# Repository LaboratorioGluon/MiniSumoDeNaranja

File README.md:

# MiniSumoDeNaranja
Minisumo para la competición OSHDEM 2023.

Hecho integramente en los directos de twitch (www.twitch.tv/labgluon)

# Hardware

## Componentes (fuera de la PCB):
- Sensores IR (TCRT5000) https://s.click.aliexpress.com/e/_DeqiwYr
- Sensores ToF (VL53L0X) https://s.click.aliexpress.com/e/_DDpGy5Z
- Motores (N20 200RPM) https://s.click.aliexpress.com/e/_DkiL8JH
- ESP32 (ESP32-WROOM-32D) https://s.click.aliexpress.com/e/_DlMmuSj

## Configuracion pines

| 1 | 2 | 3 | 4 | Modo |
|-|-|-|-|-|
| 0 | 0 | 0 | 0 | FWD  |
| 1 | 0 | 0 | 0 | RIGHT|
| 0 | 1 | 0 | 0 | LEFT |

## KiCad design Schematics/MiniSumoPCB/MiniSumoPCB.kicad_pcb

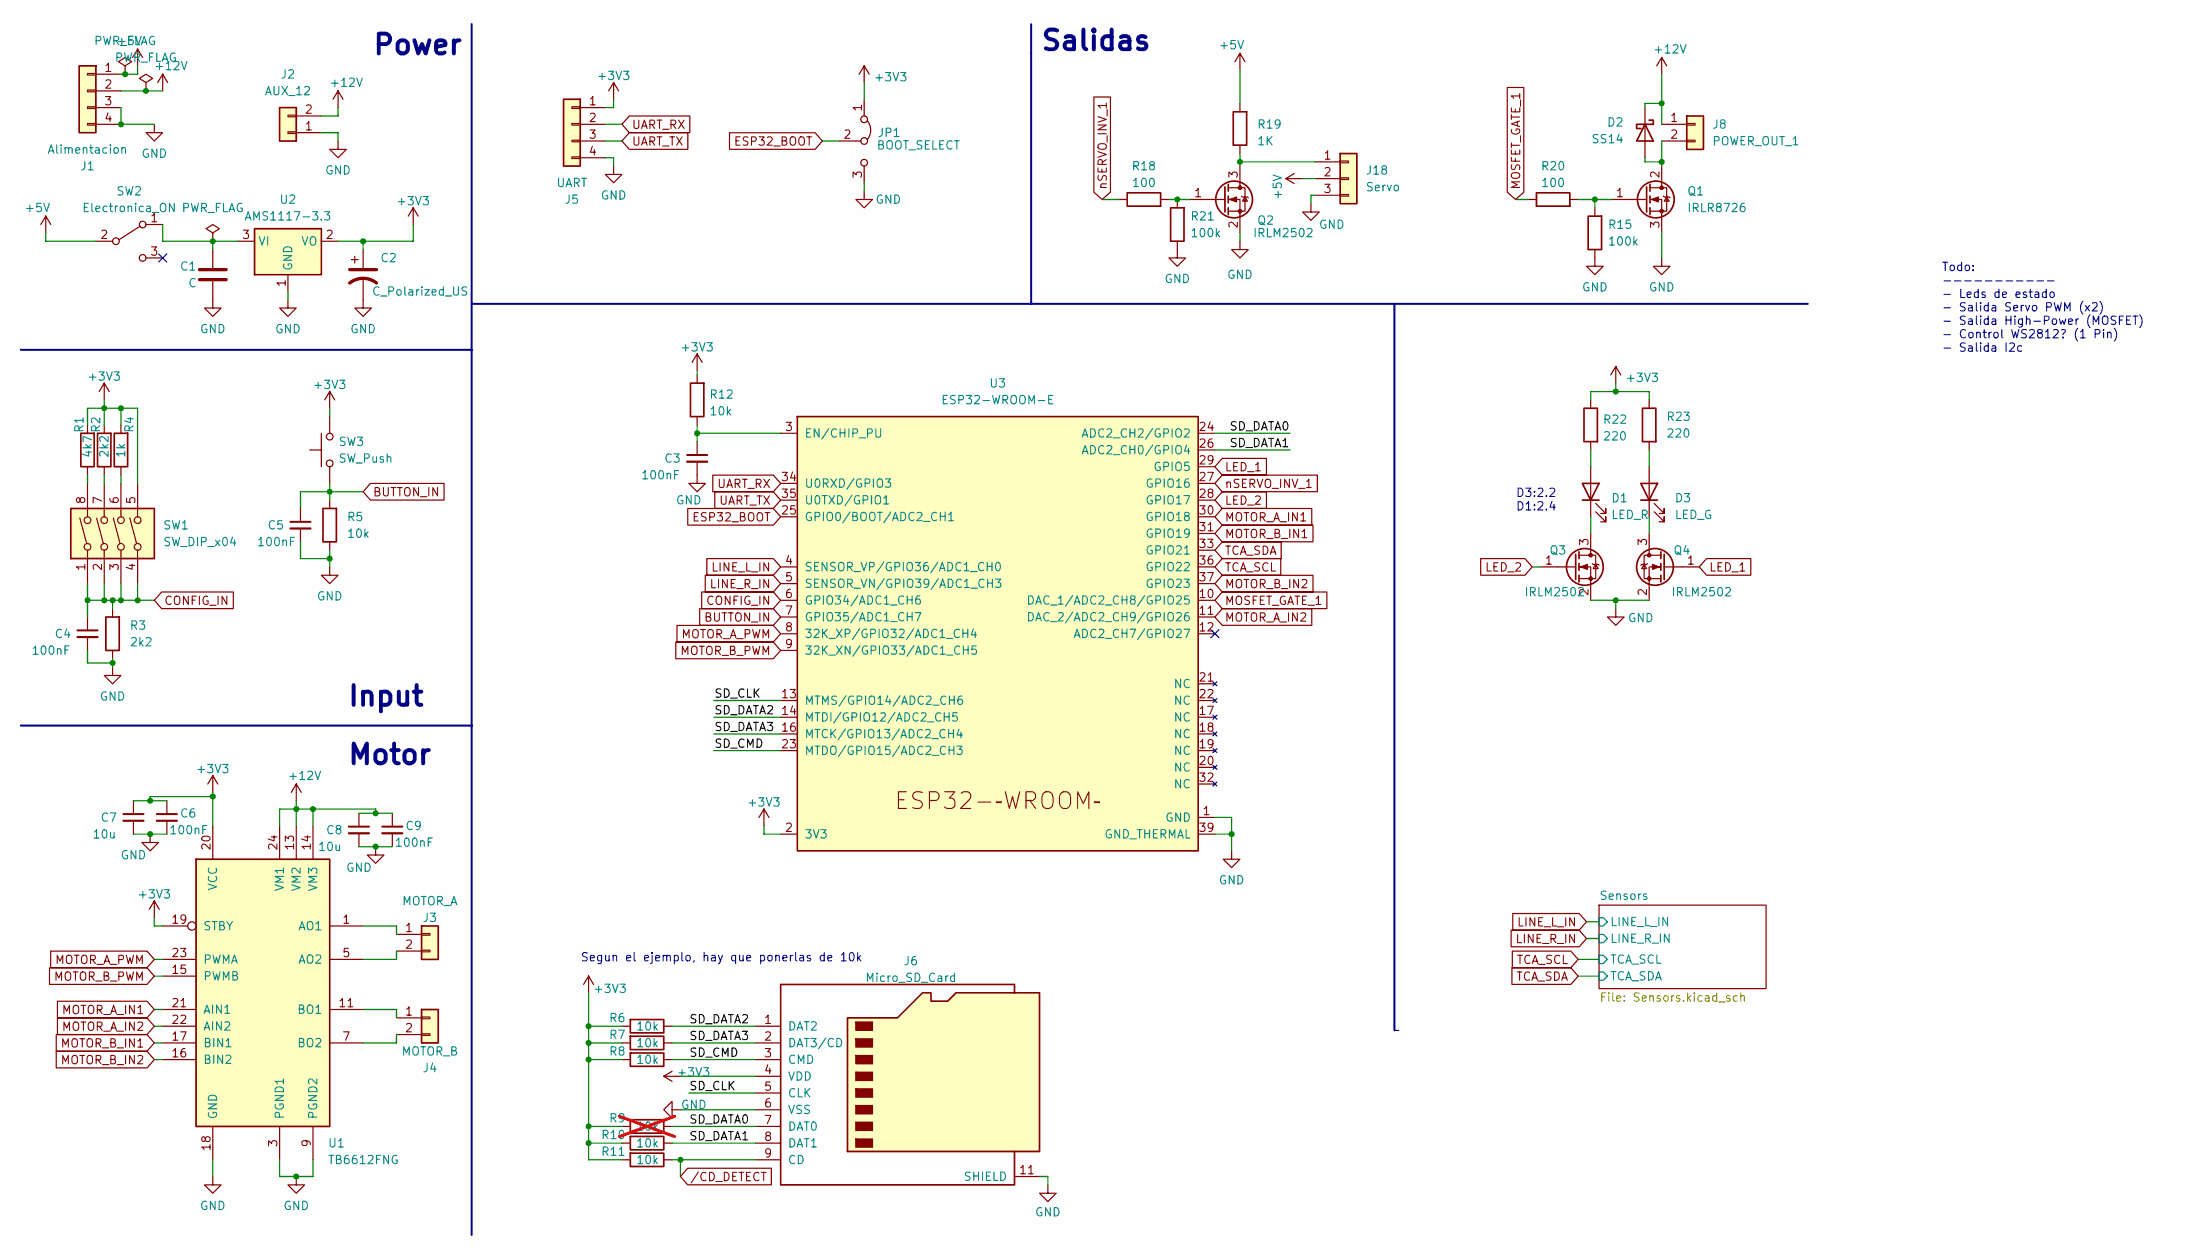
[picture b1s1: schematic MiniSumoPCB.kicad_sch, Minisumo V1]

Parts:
C1: C; C_1206_3216Metric_Pad1.33x1.80mm_HandSolder
C2: C_Polarized_US; CP_Elec_4x5.3
C3, C4, C5, C6, C9: 100nF; C_1206_3216Metric_Pad1.33x1.80mm_HandSolder
C7, C8: 10u; C_1206_3216Metric_Pad1.33x1.80mm_HandSolder
D1: LED_R; LED_1210_3225Metric_Pad1.42x2.65mm_HandSolder
D2: SS14; D_SMA_Handsoldering
D3: LED_G; LED_1210_3225Metric_Pad1.42x2.65mm_HandSolder
J1: Alimentacion; JST_PH_B4B-PH-K_1x04_P2.00mm_Vertical
J2: AUX_12; S2B-XH-SM4-TB
J3: MOTOR_A; S2B-XH-SM4-TB
J4: MOTOR_B; S2B-XH-SM4-TB
J5: UART; PinHeader_1x04_P2.54mm_Vertical
J6: Micro_SD_Card; microSD-Receptacle-SelfEject
J8: POWER_OUT_1; S2B-XH-SM4-TB
J18: Servo; PinHeader_1x03_P2.54mm_Vertical
JP1: BOOT_SELECT; PinHeader_1x03_P2.54mm_Vertical
Q1: IRLR8726; TO-252-2
Q2, Q3, Q4: IRLM2502; SOT-23
R1: 4k7; R_1206_3216Metric_Pad1.30x1.75mm_HandSolder
R2, R3: 2k2; R_1206_3216Metric_Pad1.30x1.75mm_HandSolder
R4: 1k; R_1206_3216Metric_Pad1.30x1.75mm_HandSolder
R5, R6, R7, R8, R10, R11, R12: 10k; R_1206_3216Metric_Pad1.30x1.75mm_HandSolder
R9: 10k; R_1206_3216Metric_Pad1.30x1.75mm_HandSolder; not fitted
R15, R21: 100k; R_1206_3216Metric_Pad1.30x1.75mm_HandSolder
R18, R20: 100; R_1206_3216Metric_Pad1.30x1.75mm_HandSolder
R19: 1K; R_1206_3216Metric_Pad1.30x1.75mm_HandSolder
R22, R23: 220; R_1206_3216Metric_Pad1.30x1.75mm_HandSolder
SW1: SW_DIP_x04; SW_DIP_SPSTx04_Slide_9.78x12.34mm_W7.62mm_P2.54mm
SW2: Electronica_ON; SS12D07VG2
SW3: SW_Push; SKPMANE010 _Silicone_6x6mm
U1: TB6612FNG; SSOP-24_5.3x8.2mm_P0.65mm
U2: AMS1117-3.3; SOT-223-3_TabPin2
U3: ESP32-WROOM-E; ESP32-WROOM-32E

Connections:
+3V3: C2.1, C6.1, C7.1, J5.1, J6.4 (VDD), JP1.1 (A), R1.2, R2.2, R4.2, R6.2, R7.2, R8.2, R9.2, R10.2, R11.2, R12.2, R22.1, R23.1, SW1.5, SW3.2, U1.19 (STBY), U1.20 (VCC), U2.2 (VO), U3.2 (3V3); also elsewhere on the board
+5V: J1.1, J18.2, R19.2, SW2.2 (B)
+12V: C8.1, C9.1, D2.1 (K), J1.2, J2.2, J8.1, U1.13 (VM2), U1.14 (VM3), U1.24 (VM1)
/SD_CLK: J6.5 (CLK), U3.13 (MTMS/GPIO14/ADC2_CH6)
/SD_CMD: J6.3 (CMD), R8.1, U3.23 (MTDO/GPIO15/ADC2_CH3)
/SD_DATA0: J6.7 (DAT0), R9.1, U3.24 (ADC2_CH2/GPIO2)
/SD_DATA1: J6.8 (DAT1), R10.1, U3.26 (ADC2_CH0/GPIO4)
/SD_DATA2: J6.1 (DAT2), R6.1, U3.14 (MTDI/GPIO12/ADC2_CH5)
/SD_DATA3: J6.2 (DAT3/CD), R7.1, U3.16 (MTCK/GPIO13/ADC2_CH4)
BUTTON_IN: C5.1, R5.2, SW3.1, U3.7 (GPIO35/ADC1_CH7)
CONFIG_IN: C4.1, R3.2, SW1.1, SW1.2, SW1.3, SW1.4, U3.6 (GPIO34/ADC1_CH6)
ESP32_BOOT: JP1.2 (C), U3.25 (GPIO0/BOOT/ADC2_CH1)
GND: C1.2, C2.2, C3.2, C4.2, C5.2, C6.2, C7.2, C8.2, C9.2, J1.3, J1.4, J2.1, J5.4, J6.6 (VSS), J6.11 (SHIELD), J18.3, JP1.3 (B), Q1.3 (S), Q2.2 (S), Q3.2 (S), Q4.2 (S), R3.1, R5.1, R15.1, R21.1, U1.3 (PGND1), U1.4 (PGND1), U1.9 (PGND2), U1.10 (PGND2), U1.18 (GND), U2.1 (GND), U3.1 (GND), U3.15 (GND), U3.38 (GND), U3.39 (GND_THERMAL); also elsewhere on the board
LED_1: Q4.1 (G), U3.29 (GPIO5)
LED_2: Q3.1 (G), U3.28 (GPIO17)
LINE_L_IN: U3.4 (SENSOR_VP/GPIO36/ADC1_CH0); also elsewhere on the board
LINE_R_IN: U3.5 (SENSOR_VN/GPIO39/ADC1_CH3); also elsewhere on the board
MOSFET_GATE_1: R20.1, U3.10 (DAC_1/ADC2_CH8/GPIO25)
MOTOR_A_IN1: U1.21 (AIN1), U3.30 (GPIO18)
MOTOR_A_IN2: U1.22 (AIN2), U3.11 (DAC_2/ADC2_CH9/GPIO26)
MOTOR_A_PWM: U1.23 (PWMA), U3.8 (32K_XP/GPIO32/ADC1_CH4)
MOTOR_B_IN1: U1.17 (BIN1), U3.31 (GPIO19)
MOTOR_B_IN2: U1.16 (BIN2), U3.37 (GPIO23)
MOTOR_B_PWM: U1.15 (PWMB), U3.9 (32K_XN/GPIO33/ADC1_CH5)
unnamed: D1.2 (A), R22.2
unnamed: D1.1 (K), Q3.3 (D)
unnamed: D2.2 (A), J8.2, Q1.2 (D)
unnamed: D3.2 (A), R23.2
unnamed: D3.1 (K), Q4.3 (D)
unnamed: J3.1, U1.1 (AO1), U1.2 (AO1)
unnamed: J3.2, U1.5 (AO2), U1.6 (AO2)
unnamed: J4.1, U1.11 (BO1), U1.12 (BO1)
unnamed: J4.2, U1.7 (BO2), U1.8 (BO2)
unnamed: J18.1, Q2.3 (D), R19.1
unnamed: Q1.1 (G), R15.2, R20.2
unnamed: Q2.1 (G), R18.2, R21.2
unnamed: R1.1, SW1.8
unnamed: R2.1, SW1.7
unnamed: R4.1, SW1.6
unnamed: C1.1, SW2.1 (A), U2.3 (VI)
unnamed: C3.1, R12.1, U3.3 (EN/CHIP_PU)
TCA_SCL: U3.36 (GPIO22); also elsewhere on the board
TCA_SDA: U3.33 (GPIO21); also elsewhere on the board
UART_RX: J5.2, U3.34 (U0RXD/GPIO3)
UART_TX: J5.3, U3.35 (U0TXD/GPIO1)
nSERVO_INV_1: R18.1, U3.27 (GPIO16)
/CD_DETECT: J6.9 (CD), R11.1

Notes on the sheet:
Motor
Segun el ejemplo, hay que ponerlas de 10k
Power
Salidas
D3:2.2 D1:2.4
Todo: ----------- - Leds de estado - Salida Servo PWM (x2) - Salida High-Power (MOSFET) - Control WS2812? (1 Pin) - Salida I2c
Input

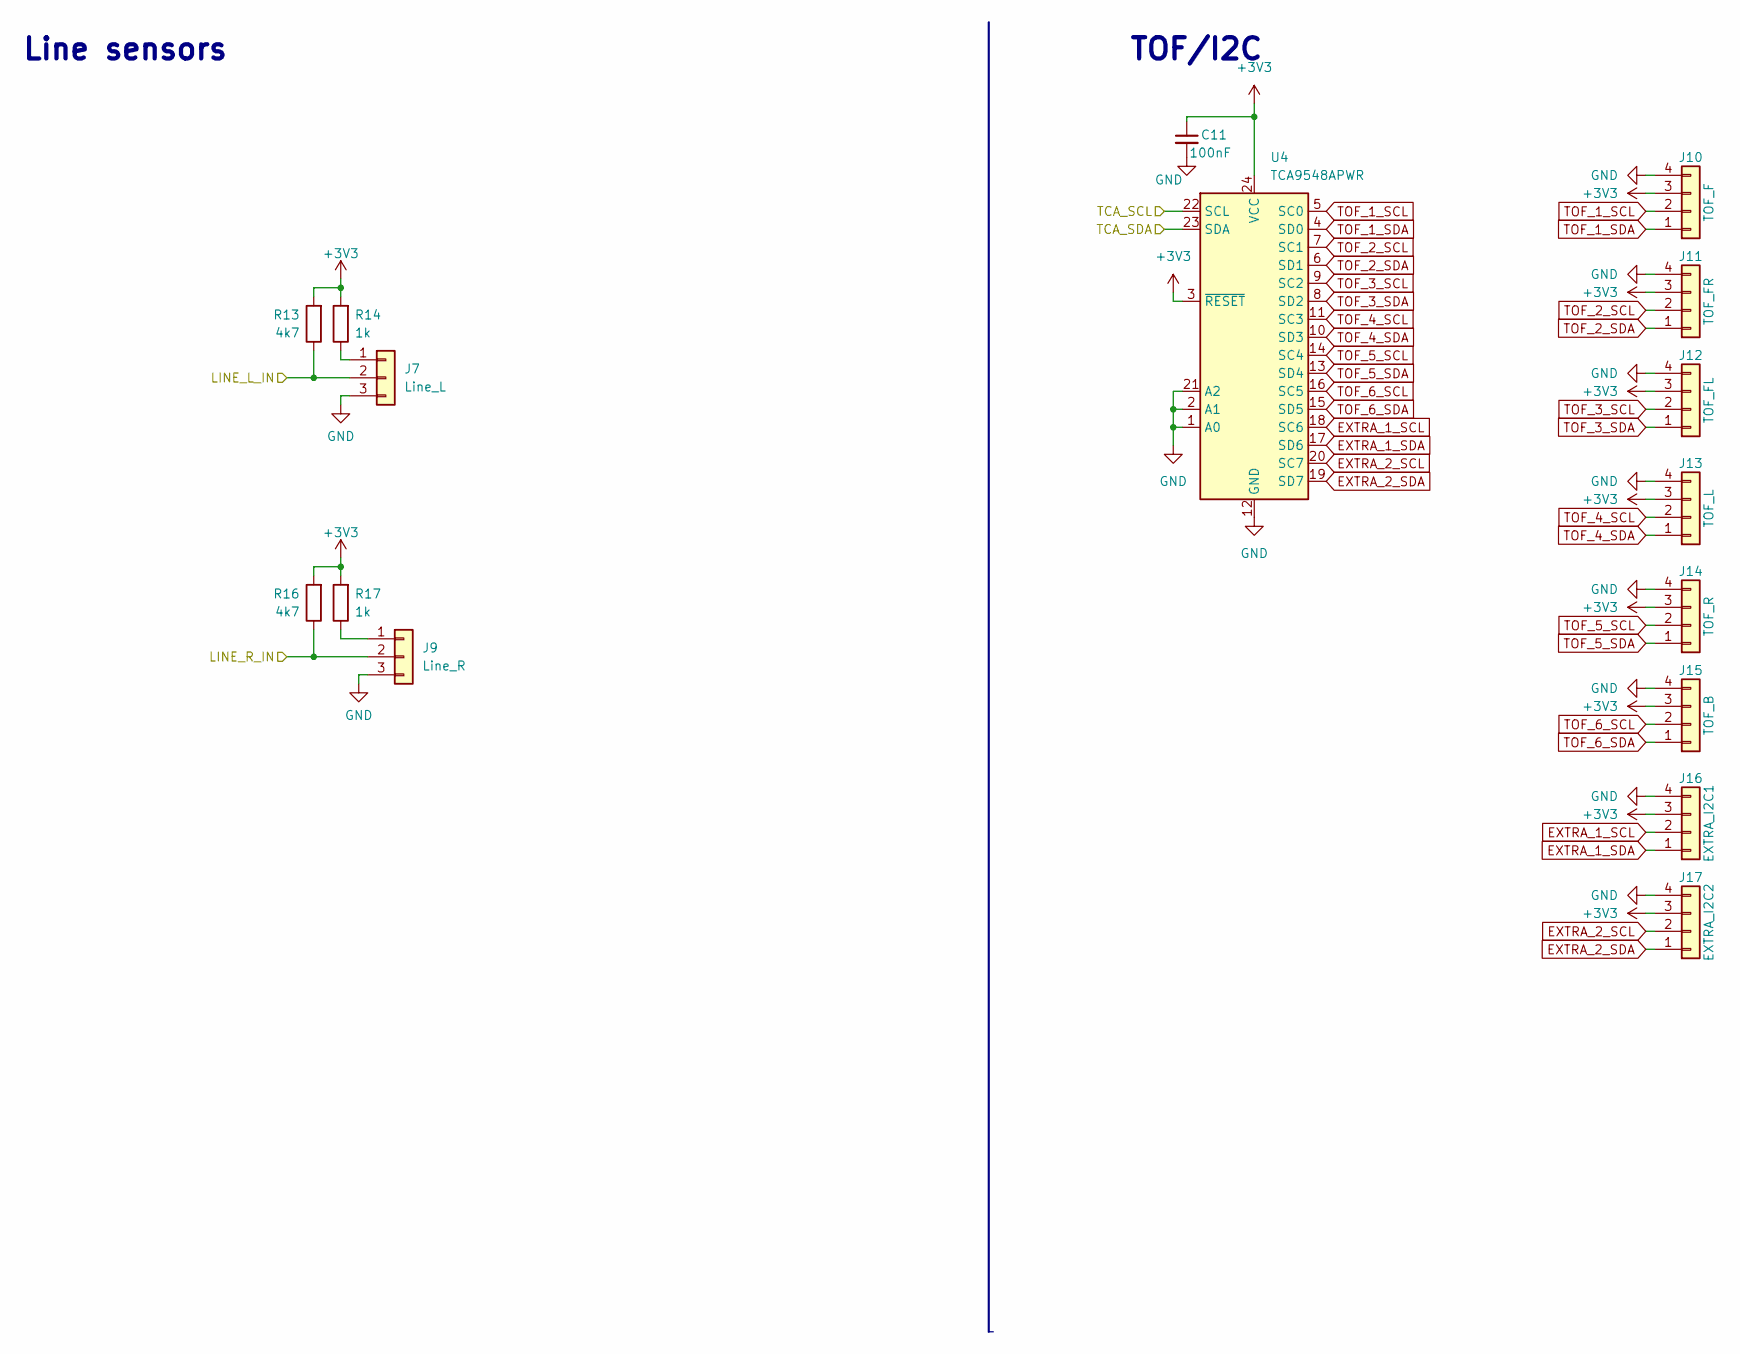
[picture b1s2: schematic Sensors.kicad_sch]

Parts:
C11: 100nF; C_1206_3216Metric_Pad1.33x1.80mm_HandSolder
J7: Line_L; JST_PH_B3B-PH-K_1x03_P2.00mm_Vertical
J9: Line_R; JST_PH_B3B-PH-K_1x03_P2.00mm_Vertical
J10: TOF_F; JST_PH_B4B-PH-K_1x04_P2.00mm_Vertical
J11: TOF_FR; JST_PH_B4B-PH-K_1x04_P2.00mm_Vertical
J12: TOF_FL; JST_PH_B4B-PH-K_1x04_P2.00mm_Vertical
J13: TOF_L; JST_PH_B4B-PH-K_1x04_P2.00mm_Vertical
J14: TOF_R; JST_PH_B4B-PH-K_1x04_P2.00mm_Vertical
J15: TOF_B; JST_PH_B4B-PH-K_1x04_P2.00mm_Vertical
J16: EXTRA_I2C1; JST_PH_B4B-PH-K_1x04_P2.00mm_Vertical
J17: EXTRA_I2C2; JST_PH_B4B-PH-K_1x04_P2.00mm_Vertical
R13, R16: 4k7; R_1206_3216Metric_Pad1.30x1.75mm_HandSolder
R14, R17: 1k; R_1206_3216Metric_Pad1.30x1.75mm_HandSolder
U4: TCA9548APWR; TSSOP-24_4.4x7.8mm_P0.65mm

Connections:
+3V3: C11.1, J10.3, J11.3, J12.3, J13.3, J14.3, J15.3, J16.3, J17.3, R13.2, R14.2, R16.2, R17.2, U4.3 (~RESET), U4.24 (VCC); also elsewhere on the board
EXTRA_1_SCL: J16.2, U4.18 (SC6)
EXTRA_1_SDA: J16.1, U4.17 (SD6)
EXTRA_2_SCL: J17.2, U4.20 (SC7)
EXTRA_2_SDA: J17.1, U4.19 (SD7)
GND: C11.2, J7.3, J9.3, J10.4, J11.4, J12.4, J13.4, J14.4, J15.4, J16.4, J17.4, U4.1 (A0), U4.2 (A1), U4.12 (GND), U4.21 (A2); also elsewhere on the board
LINE_L_IN: J7.2, R13.1; also elsewhere on the board
LINE_R_IN: J9.2, R16.1; also elsewhere on the board
unnamed: J7.1, R14.1
unnamed: J9.1, R17.1
TCA_SCL: U4.22 (SCL); also elsewhere on the board
TCA_SDA: U4.23 (SDA); also elsewhere on the board
TOF_1_SCL: J10.2, U4.5 (SC0)
TOF_1_SDA: J10.1, U4.4 (SD0)
TOF_2_SCL: J11.2, U4.7 (SC1)
TOF_2_SDA: J11.1, U4.6 (SD1)
TOF_3_SCL: J12.2, U4.9 (SC2)
TOF_3_SDA: J12.1, U4.8 (SD2)
TOF_4_SCL: J13.2, U4.11 (SC3)
TOF_4_SDA: J13.1, U4.10 (SD3)
TOF_5_SCL: J14.2, U4.14 (SC4)
TOF_5_SDA: J14.1, U4.13 (SD4)
TOF_6_SCL: J15.2, U4.16 (SC5)
TOF_6_SDA: J15.1, U4.15 (SD5)

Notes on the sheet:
Line sensors
TOF/I2C

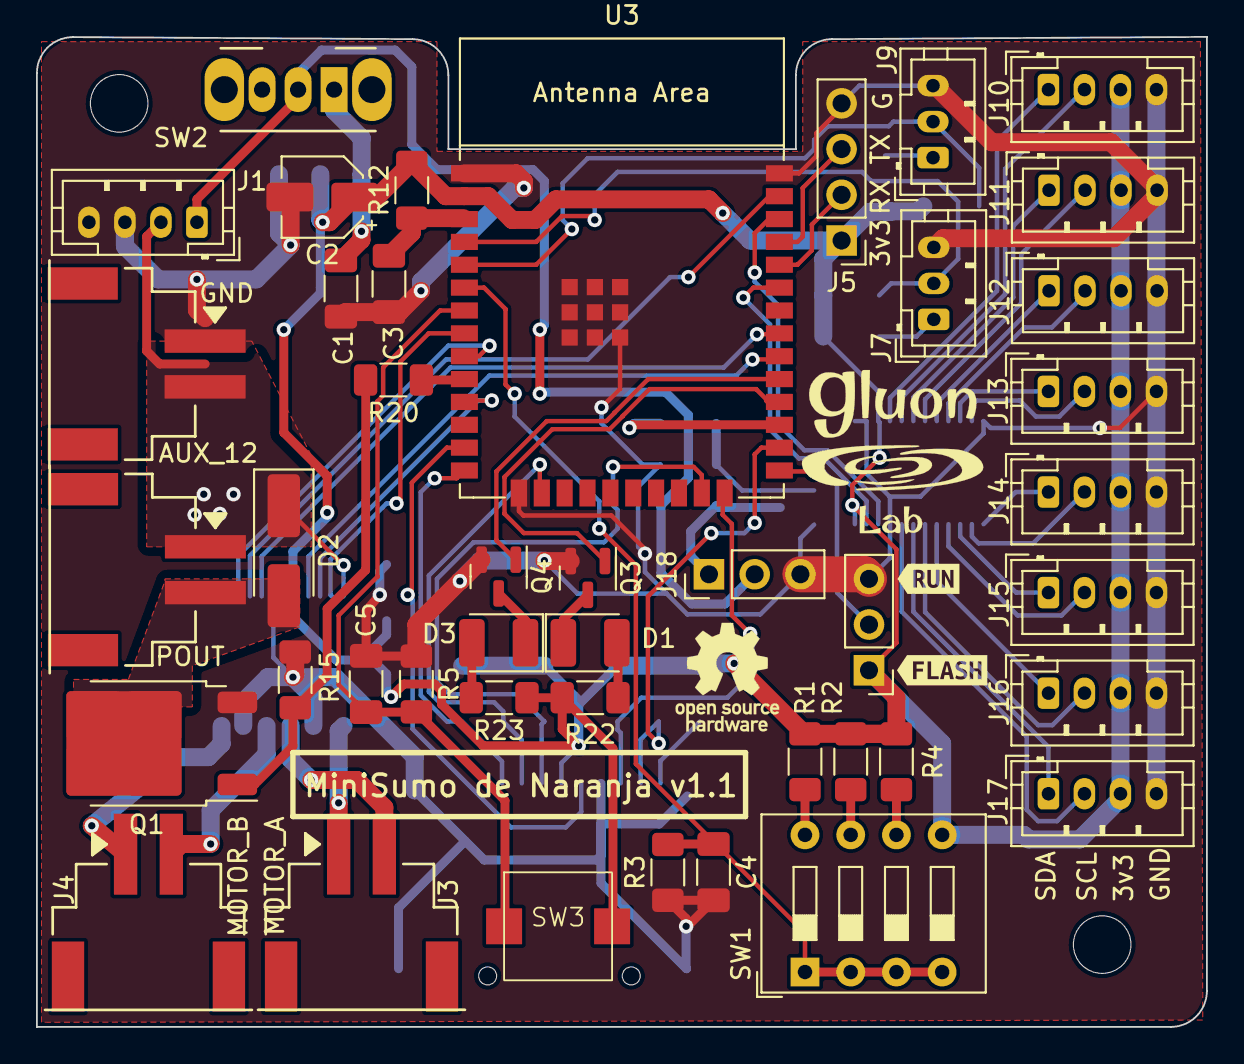
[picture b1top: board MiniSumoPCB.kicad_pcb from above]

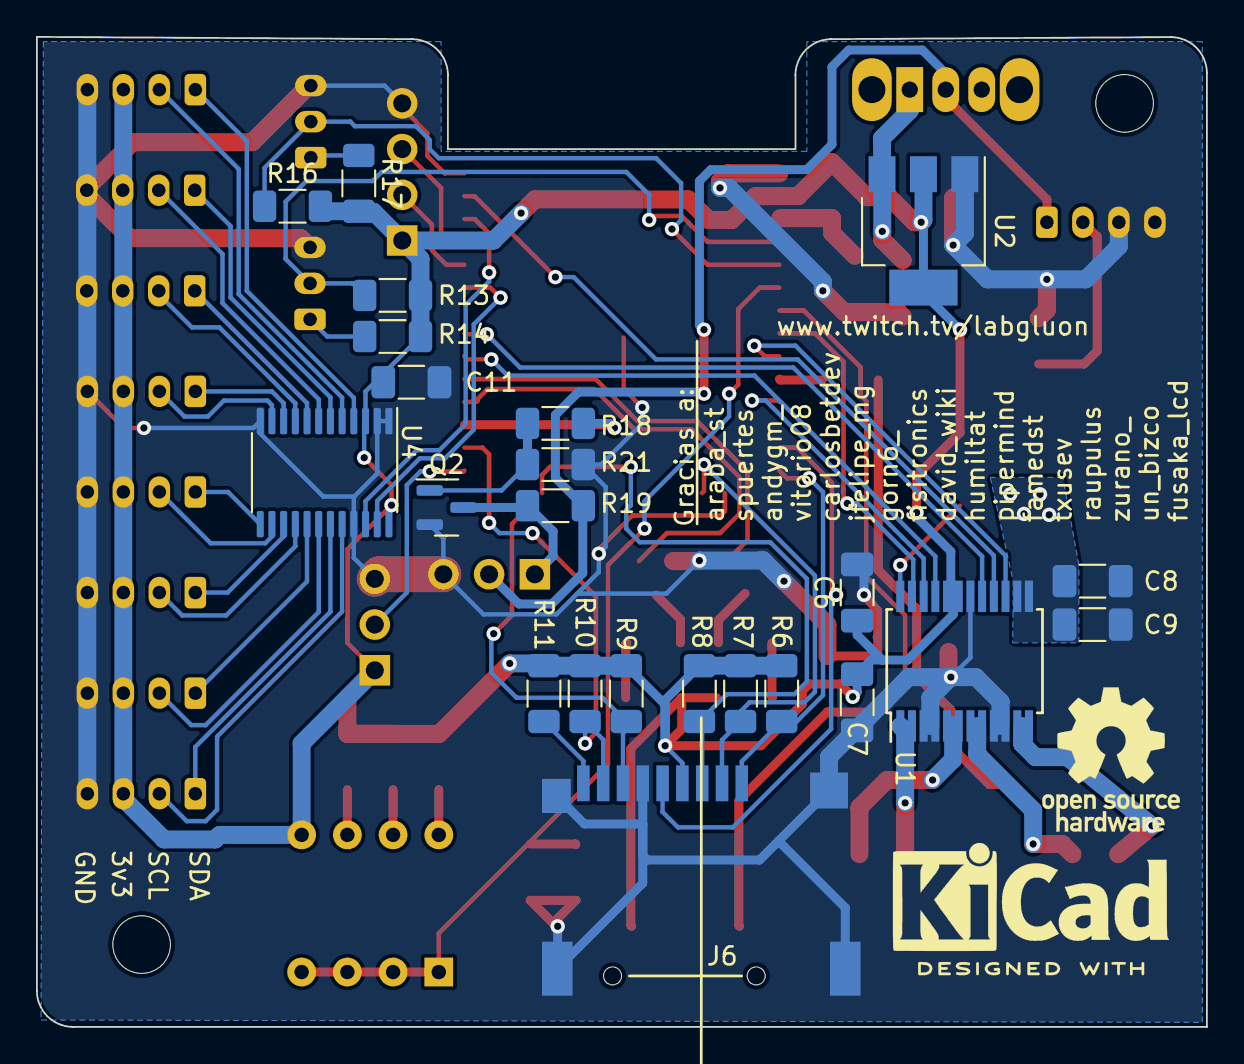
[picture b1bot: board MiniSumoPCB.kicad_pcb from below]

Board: 2 copper layers, 65.0 x 55.0 mm, 68 parts (23 on the bottom side), 65 nets.

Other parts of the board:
kibuzzard-63F11F4E: G***; kibuzzard-63F11F4E
kibuzzard-63F11F5A: G***; kibuzzard-63F11F5A

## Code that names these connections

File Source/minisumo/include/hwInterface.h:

// Pinout for U3 (ESP32-WROOM-E)
// #define PIN_GND 
// #define PIN_P3V3 
#define PIN_NETNU3NENSLASHCHIP_PU 
#define PIN_LINE_L_IN GPIO_NUM_36
#define PIN_LINE_R_IN GPIO_NUM_39
#define PIN_CONFIG_IN GPIO_NUM_34
#define PIN_BUTTON_IN GPIO_NUM_35
#define PIN_MOTOR_A_PWM GPIO_NUM_32
#define PIN_MOTOR_B_PWM GPIO_NUM_33
#define PIN_MOSFET_GATE_1 GPIO_NUM_25
#define PIN_MOTOR_A_IN2 GPIO_NUM_26
// #define PIN_UNCONNECTEDNU3NADC2_CH7SLASHGPIO27NPAD12 GPIO_NUM_27
#define PIN_SD_CLK GPIO_NUM_14
#define PIN_SD_DATA2 GPIO_NUM_12
#define PIN_GND 
#define PIN_SD_DATA3 GPIO_NUM_13
// #define PIN_UNCONNECTEDNU3NNCNPAD17 
// #define PIN_UNCONNECTEDNU3NNCNPAD18 
// #define PIN_UNCONNECTEDNU3NNCNPAD19 
// #define PIN_UNCONNECTEDNU3NNCNPAD20 
// #define PIN_UNCONNECTEDNU3NNCNPAD21 
// #define PIN_UNCONNECTEDNU3NNCNPAD22 
#define PIN_SD_CMD GPIO_NUM_15
#define PIN_SD_DATA0 GPIO_NUM_2
#define PIN_ESP32_BOOT GPIO_NUM_0
#define PIN_SD_DATA1 GPIO_NUM_4
#define PIN_NSERVO_INV_1 GPIO_NUM_16
#define PIN_LED_2 GPIO_NUM_17
#define PIN_LED_1 GPIO_NUM_5
#define PIN_MOTOR_A_IN1 GPIO_NUM_18
#define PIN_MOTOR_B_IN1 GPIO_NUM_19
// #define PIN_UNCONNECTEDNU3NNCNPAD32 
#define PIN_TCA_SDA GPIO_NUM_21
#define PIN_UART_RX GPIO_NUM_3
#define PIN_UART_TX GPIO_NUM_1
#define PIN_TCA_SCL GPIO_NUM_22
#define PIN_MOTOR_B_IN2 GPIO_NUM_23
// #define PIN_GND 
// #define PIN_GND 

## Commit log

2023-08-13 WIP Source code
2023-08-13 Added PCB design
2023-08-13 Added hooks
2023-08-13 Added hooks updated
2023-08-14 Improved Hook for pdf
2023-08-14 Added new subs to PCB
2023-08-14 Create LICENSE
2023-08-14 [PCB] Added decoupling Capacitors
2023-08-15 [PCB] Update minor version
2023-08-20 Two cores and mutex working
2023-08-20 Tof sensor data used in FSM
2023-08-23 Code cleanup
2023-09-15 Added Tb661.. driver and push button detection
2023-09-15 Added LED information
2023-09-21 Working sensors and wheel! First robot build
2023-09-24 Forking line sensor avoidance
2023-10-01 Update README.md to add components
2023-10-03 Target tracking
2023-10-03 Added HW schematic
2023-10-05 Rotation fix
2023-10-05 At least it tries to attack!
2023-10-05 Prepared for battle
2023-10-06 Added 3d model parts
2023-12-16 Resistor Ladder
